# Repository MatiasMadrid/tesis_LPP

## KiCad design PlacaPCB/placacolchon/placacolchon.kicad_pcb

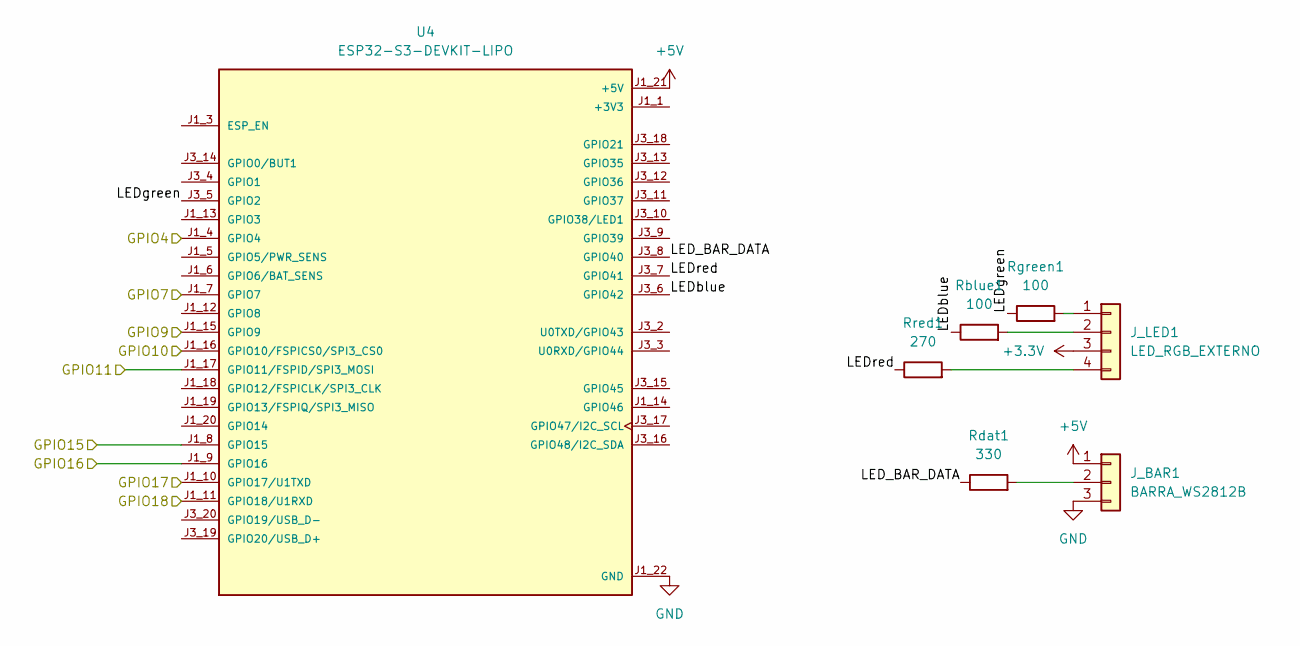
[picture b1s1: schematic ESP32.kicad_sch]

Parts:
J_BAR1: BARRA_WS2812B; PinHeader_1x03_P2.54mm_Vertical
J_LED1: LED_RGB_EXTERNO; PinHeader_1x04_P2.54mm_Vertical
Rblue1: 100; R_0805_2012Metric
Rdat1: 330; R_0805_2012Metric
Rgreen1: 100; R_0805_2012Metric
Rred1: 270; R_0805_2012Metric
U4: ESP32-S3-DEVKIT-LIPO; XCVR_ESP32-S3-DEVKIT-LIPO; PARTREV B

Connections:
+3.3V: J_LED1.3; also elsewhere on the board
+3V3: U4.J1_1 (+3V3), U4.J1_2 (+3V3)
+5V: J_BAR1.1, U4.J1_21 (+5V); also elsewhere on the board
/AnalogSens/GPIO4: U4.J1_4 (GPIO4); also elsewhere on the board
/AnalogSens/GPIO7: U4.J1_7 (GPIO7); also elsewhere on the board
/AnalogSens/GPIO9: U4.J1_15 (GPIO9); also elsewhere on the board
/AnalogSens/GPIO10: U4.J1_16 (GPIO10/FSPICS0/SPI3_CS0); also elsewhere on the board
/AnalogSens/GPIO11: U4.J1_17 (GPIO11/FSPID/SPI3_MOSI); also elsewhere on the board
/AnalogSens/GPIO15: U4.J1_8 (GPIO15); also elsewhere on the board
/AnalogSens/GPIO16: U4.J1_9 (GPIO16); also elsewhere on the board
/AnalogSens/GPIO17: U4.J1_10 (GPIO17/U1TXD); also elsewhere on the board
/AnalogSens/GPIO18: U4.J1_11 (GPIO18/U1RXD); also elsewhere on the board
/ESP32/LED_BAR_DATA: Rdat1.1, U4.J3_8 (GPIO40)
/ESP32/LEDblue: Rblue1.1, U4.J3_6 (GPIO42)
/ESP32/LEDgreen: Rgreen1.1, U4.J3_5 (GPIO2)
/ESP32/LEDred: Rred1.1, U4.J3_7 (GPIO41)
GND: J_BAR1.3, U4.J1_22 (GND), U4.J3_1 (GND), U4.J3_21 (GND), U4.J3_22 (GND); also elsewhere on the board
unnamed: J_BAR1.2, Rdat1.2
unnamed: J_LED1.1, Rgreen1.2
unnamed: J_LED1.2, Rblue1.2
unnamed: J_LED1.4, Rred1.2

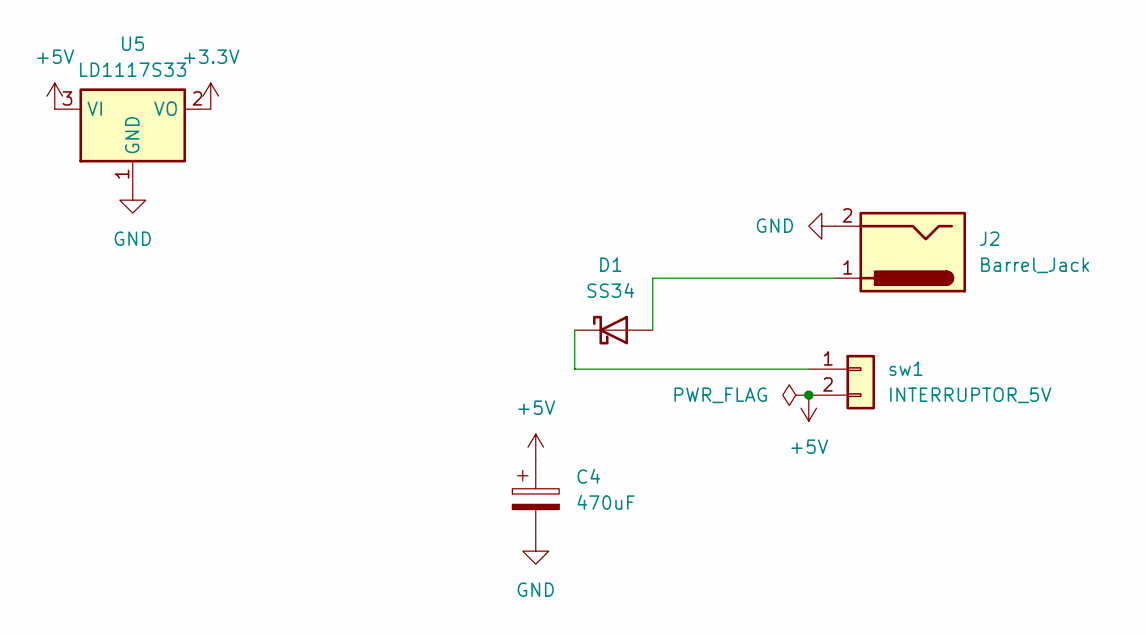
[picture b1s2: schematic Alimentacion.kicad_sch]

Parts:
C4: 470uF; CP_Radial_D8.0mm_P3.50mm
D1: SS34; D_SMA
J2: Barrel_Jack; BarrelJack_Horizontal
U5: LD1117S33; SOT-223-3_TabPin2
sw1: INTERRUPTOR_5V; PinHeader_1x02_P2.54mm_Vertical

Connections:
+3.3V: U5.2 (VO); also elsewhere on the board
+5V: C4.1, U5.3 (VI), sw1.2; also elsewhere on the board
GND: C4.2, J2.2, U5.1 (GND); also elsewhere on the board
unnamed: D1.2 (A), J2.1
unnamed: D1.1 (K), sw1.1

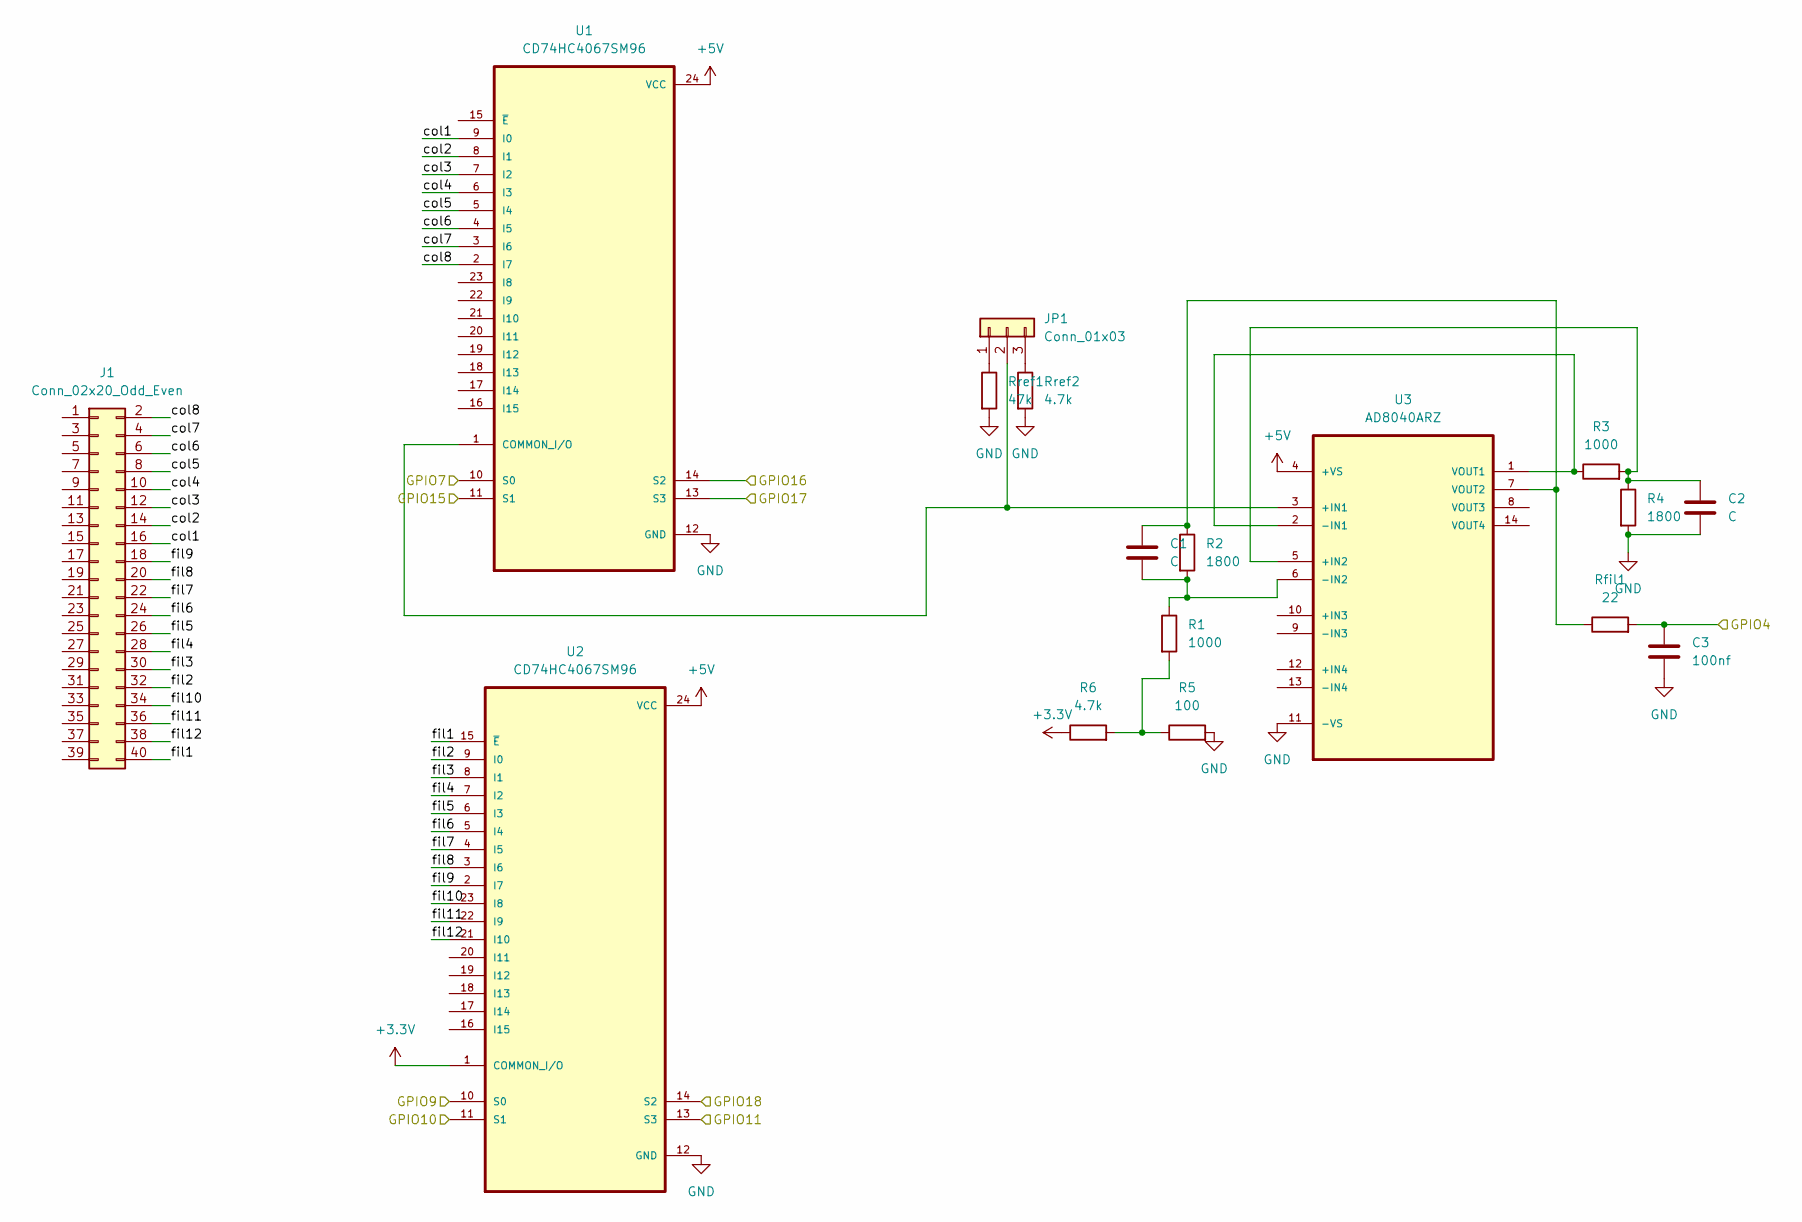
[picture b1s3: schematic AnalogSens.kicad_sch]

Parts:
C1, C2: C; C_0805_2012Metric
C3: 100nf; C_0805_2012Metric
J1: Conn_02x20_Odd_Even; IDC-Header_2x20_P2.54mm_Vertical
JP1: Conn_01x03; PinHeader_1x03_P2.54mm_Vertical
R1, R3: 1000; R_0805_2012Metric
R2, R4: 1800; R_0805_2012Metric
R5: 100; R_0805_2012Metric
R6: 4.7k; R_0805_2012Metric
Rfil1: 22; R_0805_2012Metric
Rref1: 47k; R_0805_2012Metric
Rref2: 4.7k; R_0805_2012Metric
U1, U2: CD74HC4067SM96; SOP65P780X200-24N
U3: AD8040ARZ; SOIC127P600X175-14N; MPN AD8040ARZ

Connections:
+3.3V: R6.1, U2.1 (COMMON_I/O); also elsewhere on the board
+5V: U1.24 (VCC), U2.24 (VCC), U3.4 (+VS); also elsewhere on the board
/AnalogSens/GPIO4: C3.1, Rfil1.2; also elsewhere on the board
/AnalogSens/GPIO7: U1.10 (S0); also elsewhere on the board
/AnalogSens/GPIO9: U2.10 (S0); also elsewhere on the board
/AnalogSens/GPIO10: U2.11 (S1); also elsewhere on the board
/AnalogSens/GPIO11: U2.13 (S3); also elsewhere on the board
/AnalogSens/GPIO15: U1.11 (S1); also elsewhere on the board
/AnalogSens/GPIO16: U1.14 (S2); also elsewhere on the board
/AnalogSens/GPIO17: U1.13 (S3); also elsewhere on the board
/AnalogSens/GPIO18: U2.14 (S2); also elsewhere on the board
/AnalogSens/col1: J1.16, U1.9 (I0)
/AnalogSens/col2: J1.14, U1.8 (I1)
/AnalogSens/col3: J1.12, U1.7 (I2)
/AnalogSens/col4: J1.10, U1.6 (I3)
/AnalogSens/col5: J1.8, U1.5 (I4)
/AnalogSens/col6: J1.6, U1.4 (I5)
/AnalogSens/col7: J1.4, U1.3 (I6)
/AnalogSens/col8: J1.2, U1.2 (I7)
/AnalogSens/fil1: J1.40, U2.15 (~E)
/AnalogSens/fil2: J1.32, U2.9 (I0)
/AnalogSens/fil3: J1.30, U2.8 (I1)
/AnalogSens/fil4: J1.28, U2.7 (I2)
/AnalogSens/fil5: J1.26, U2.6 (I3)
/AnalogSens/fil6: J1.24, U2.5 (I4)
/AnalogSens/fil7: J1.22, U2.4 (I5)
/AnalogSens/fil8: J1.20, U2.3 (I6)
/AnalogSens/fil9: J1.18, U2.2 (I7)
/AnalogSens/fil10: J1.34, U2.23 (I8)
/AnalogSens/fil11: J1.36, U2.22 (I9)
/AnalogSens/fil12: J1.38, U2.21 (I10)
GND: C2.2, C3.2, R4.2, R5.2, Rref1.2, Rref2.2, U1.12 (GND), U2.12 (GND), U3.11 (-VS); also elsewhere on the board
unnamed: JP1.1, Rref1.1
unnamed: JP1.2, U1.1 (COMMON_I/O), U3.3 (+IN1)
unnamed: JP1.3, Rref2.1
unnamed: R1.2, R5.1, R6.2
unnamed: C2.1, R3.2, R4.1, U3.5 (+IN2)
unnamed: R3.1, U3.1 (VOUT1), U3.2 (-IN1)
unnamed: C1.2, R1.1, R2.2, U3.6 (-IN2)
unnamed: C1.1, R2.1, Rfil1.1, U3.7 (VOUT2)

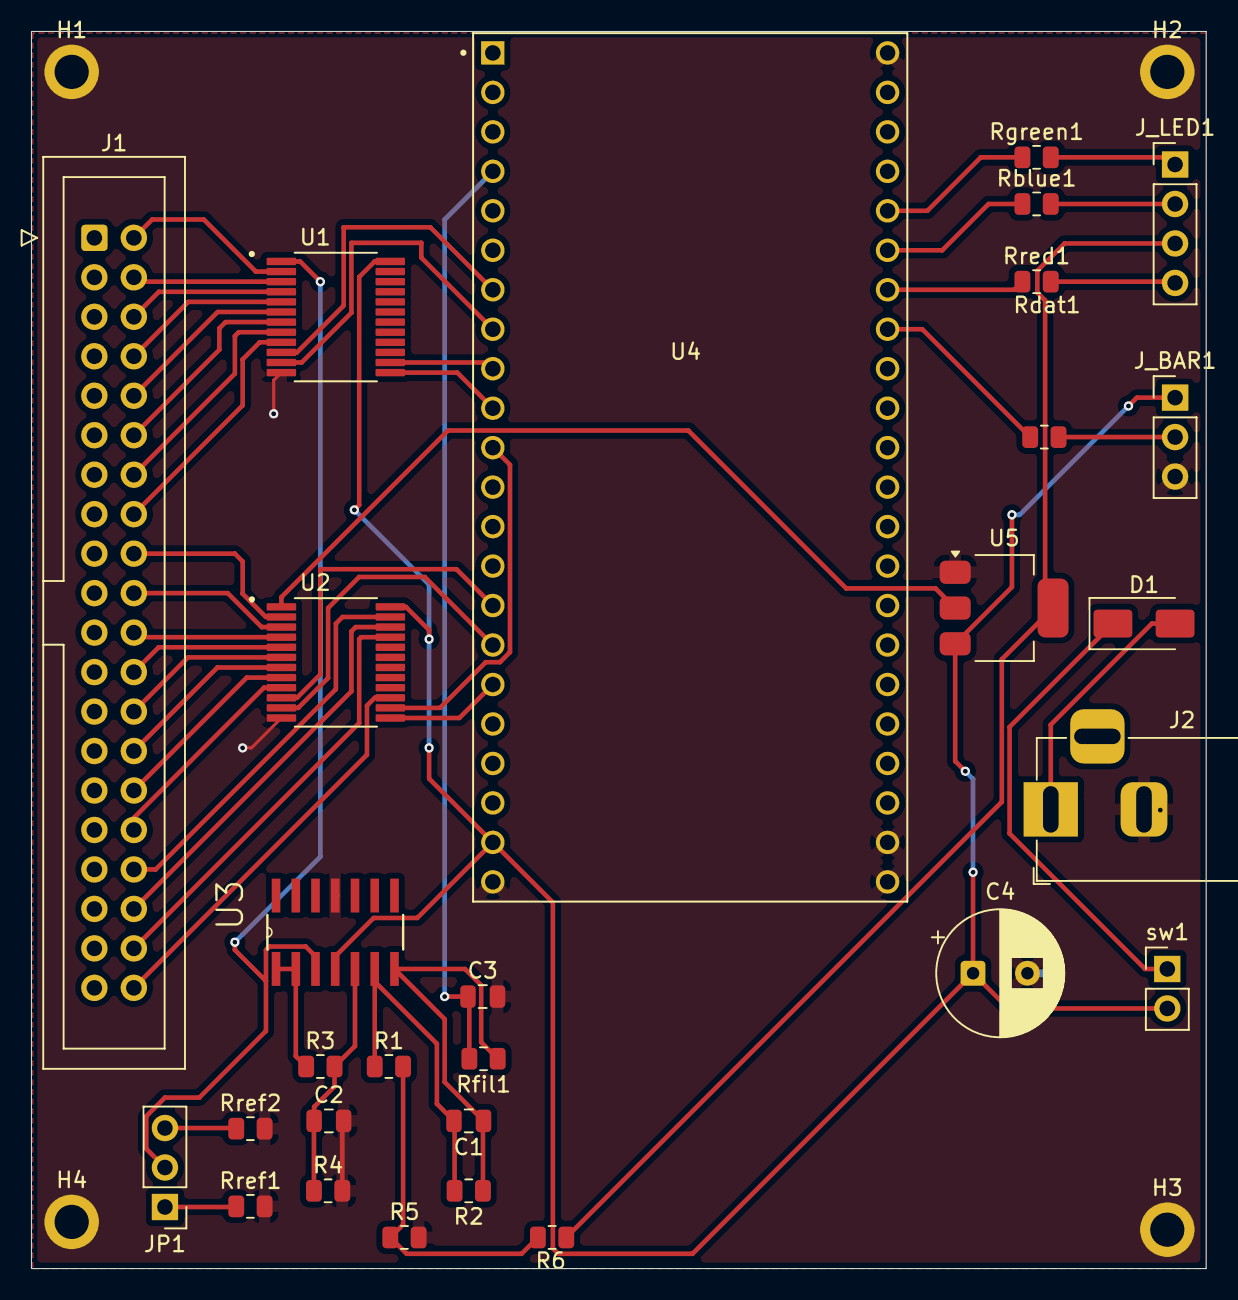
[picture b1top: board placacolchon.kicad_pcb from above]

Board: 2 copper layers, 75.6 x 79.6 mm, 33 parts (0 on the bottom side), 51 nets.

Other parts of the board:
H1, H2, H3, H4: MountingHole_2.2mm_M2_ISO7380_Pad

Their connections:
GND: H1.1, H2.2, H3.3, H4.4; also elsewhere on the board
